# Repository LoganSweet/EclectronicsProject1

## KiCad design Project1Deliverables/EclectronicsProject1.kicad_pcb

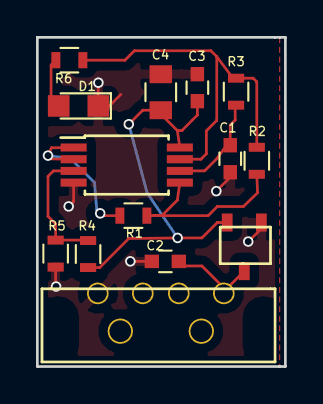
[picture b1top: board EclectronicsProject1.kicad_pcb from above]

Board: 2 copper layers, 13.8 x 18.3 mm, 11 parts (0 on the bottom side), 7 nets.

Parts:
C1, C2, C3: C_0603
C4: C_0805
D1: LED_0805
R1, R2, R3, R4, R5, R6: R_0603

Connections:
/VDD: C3.1, C4.1, R5.1
GND: C1.2, C2.2, C3.2, C4.2, D1.1, R4.2
unnamed: C1.1, R3.2
unnamed: D1.2, R6.1
unnamed: R1.1, R2.2
unnamed: R2.1, R3.1, R6.2
unnamed: R4.1, R5.2

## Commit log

2017-10-08 Upload files from computer
